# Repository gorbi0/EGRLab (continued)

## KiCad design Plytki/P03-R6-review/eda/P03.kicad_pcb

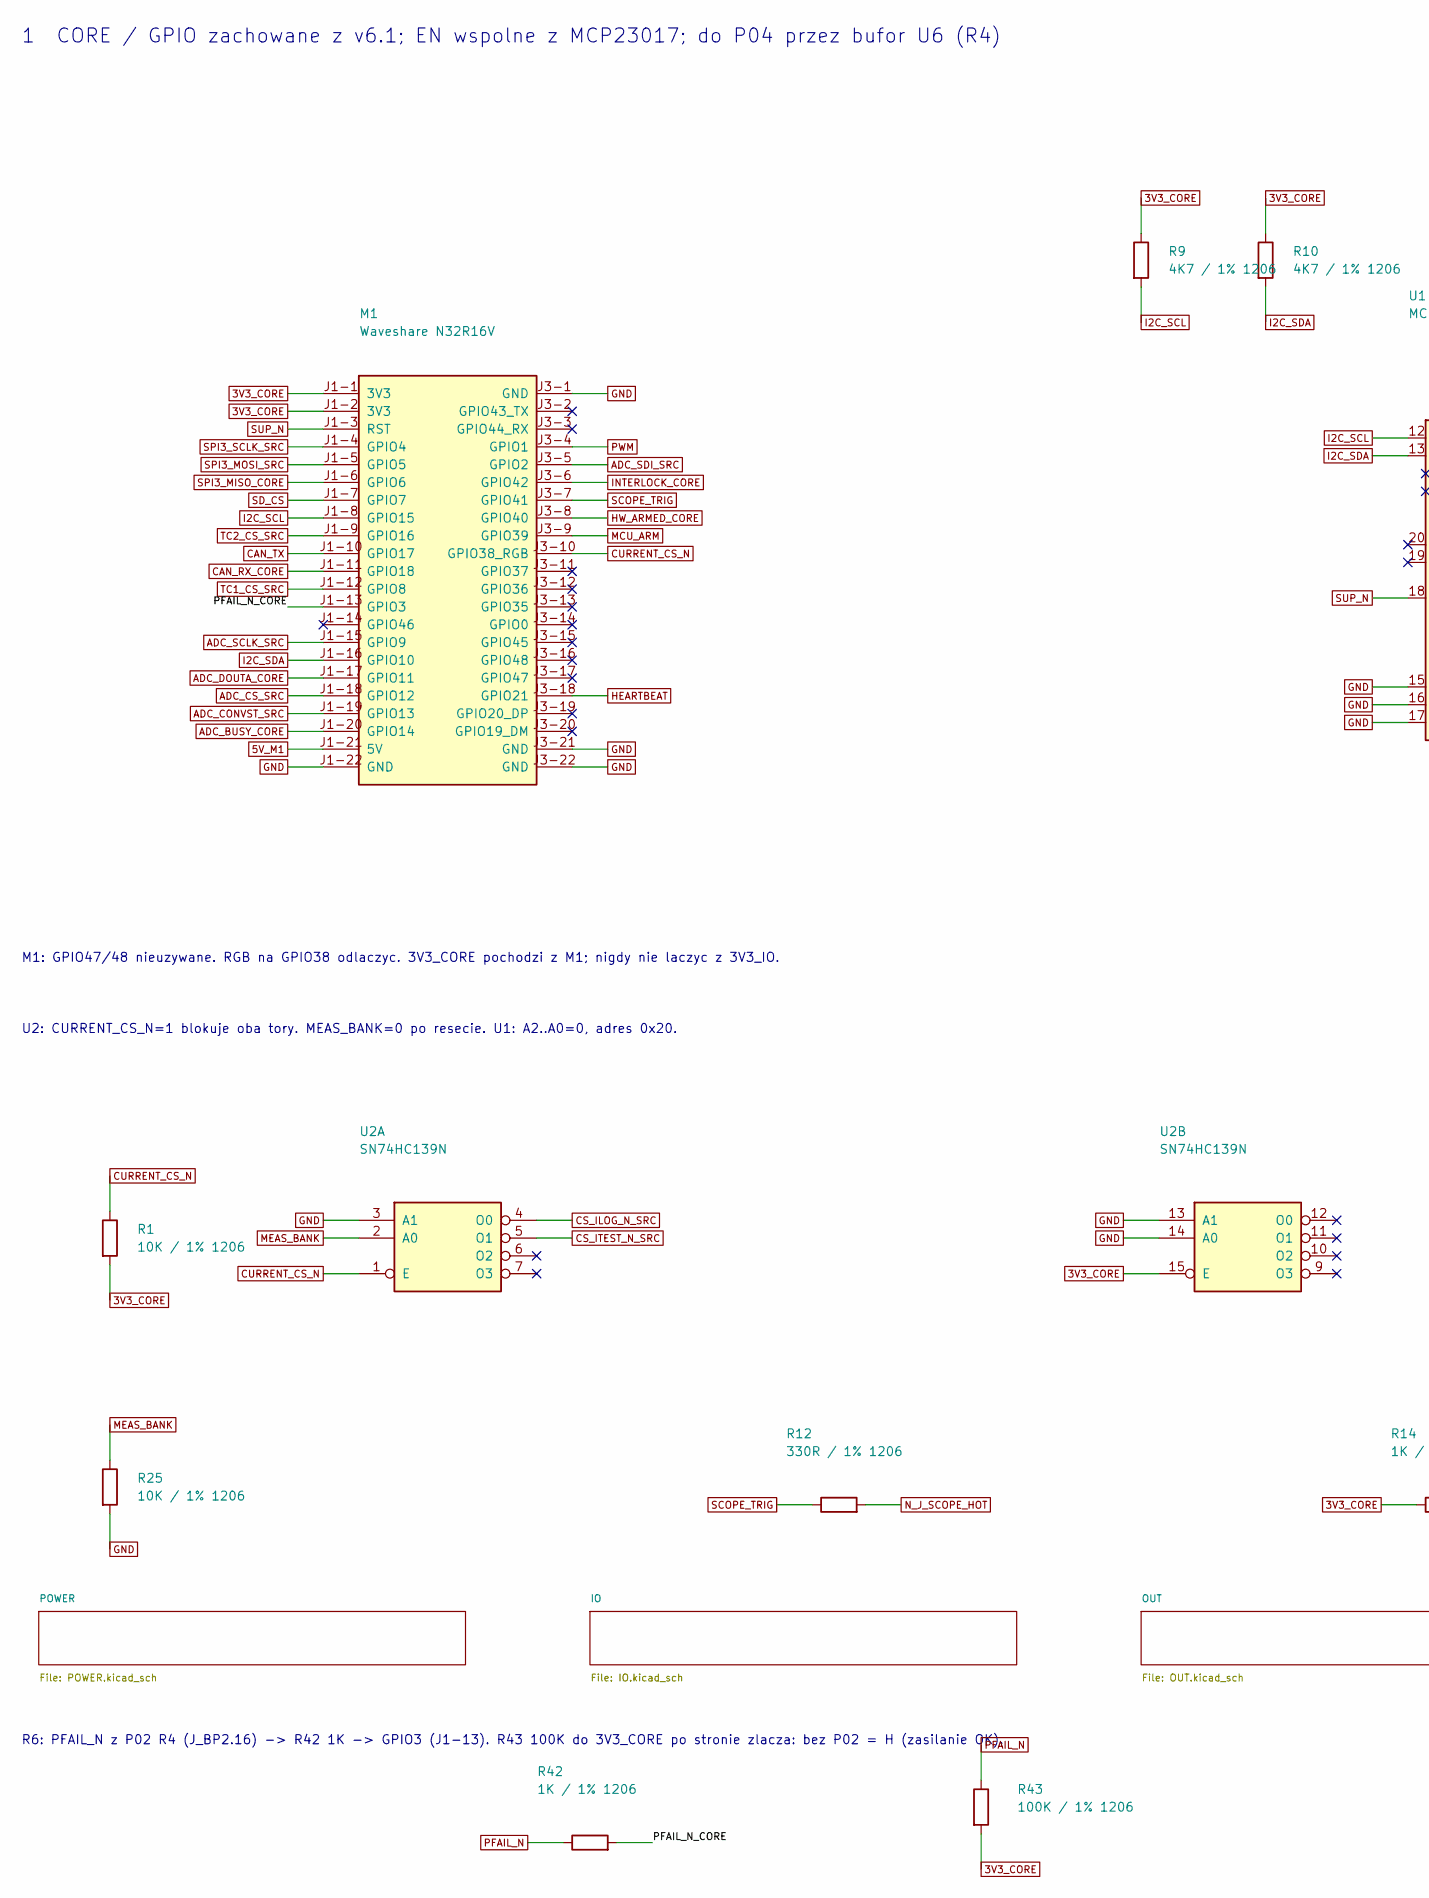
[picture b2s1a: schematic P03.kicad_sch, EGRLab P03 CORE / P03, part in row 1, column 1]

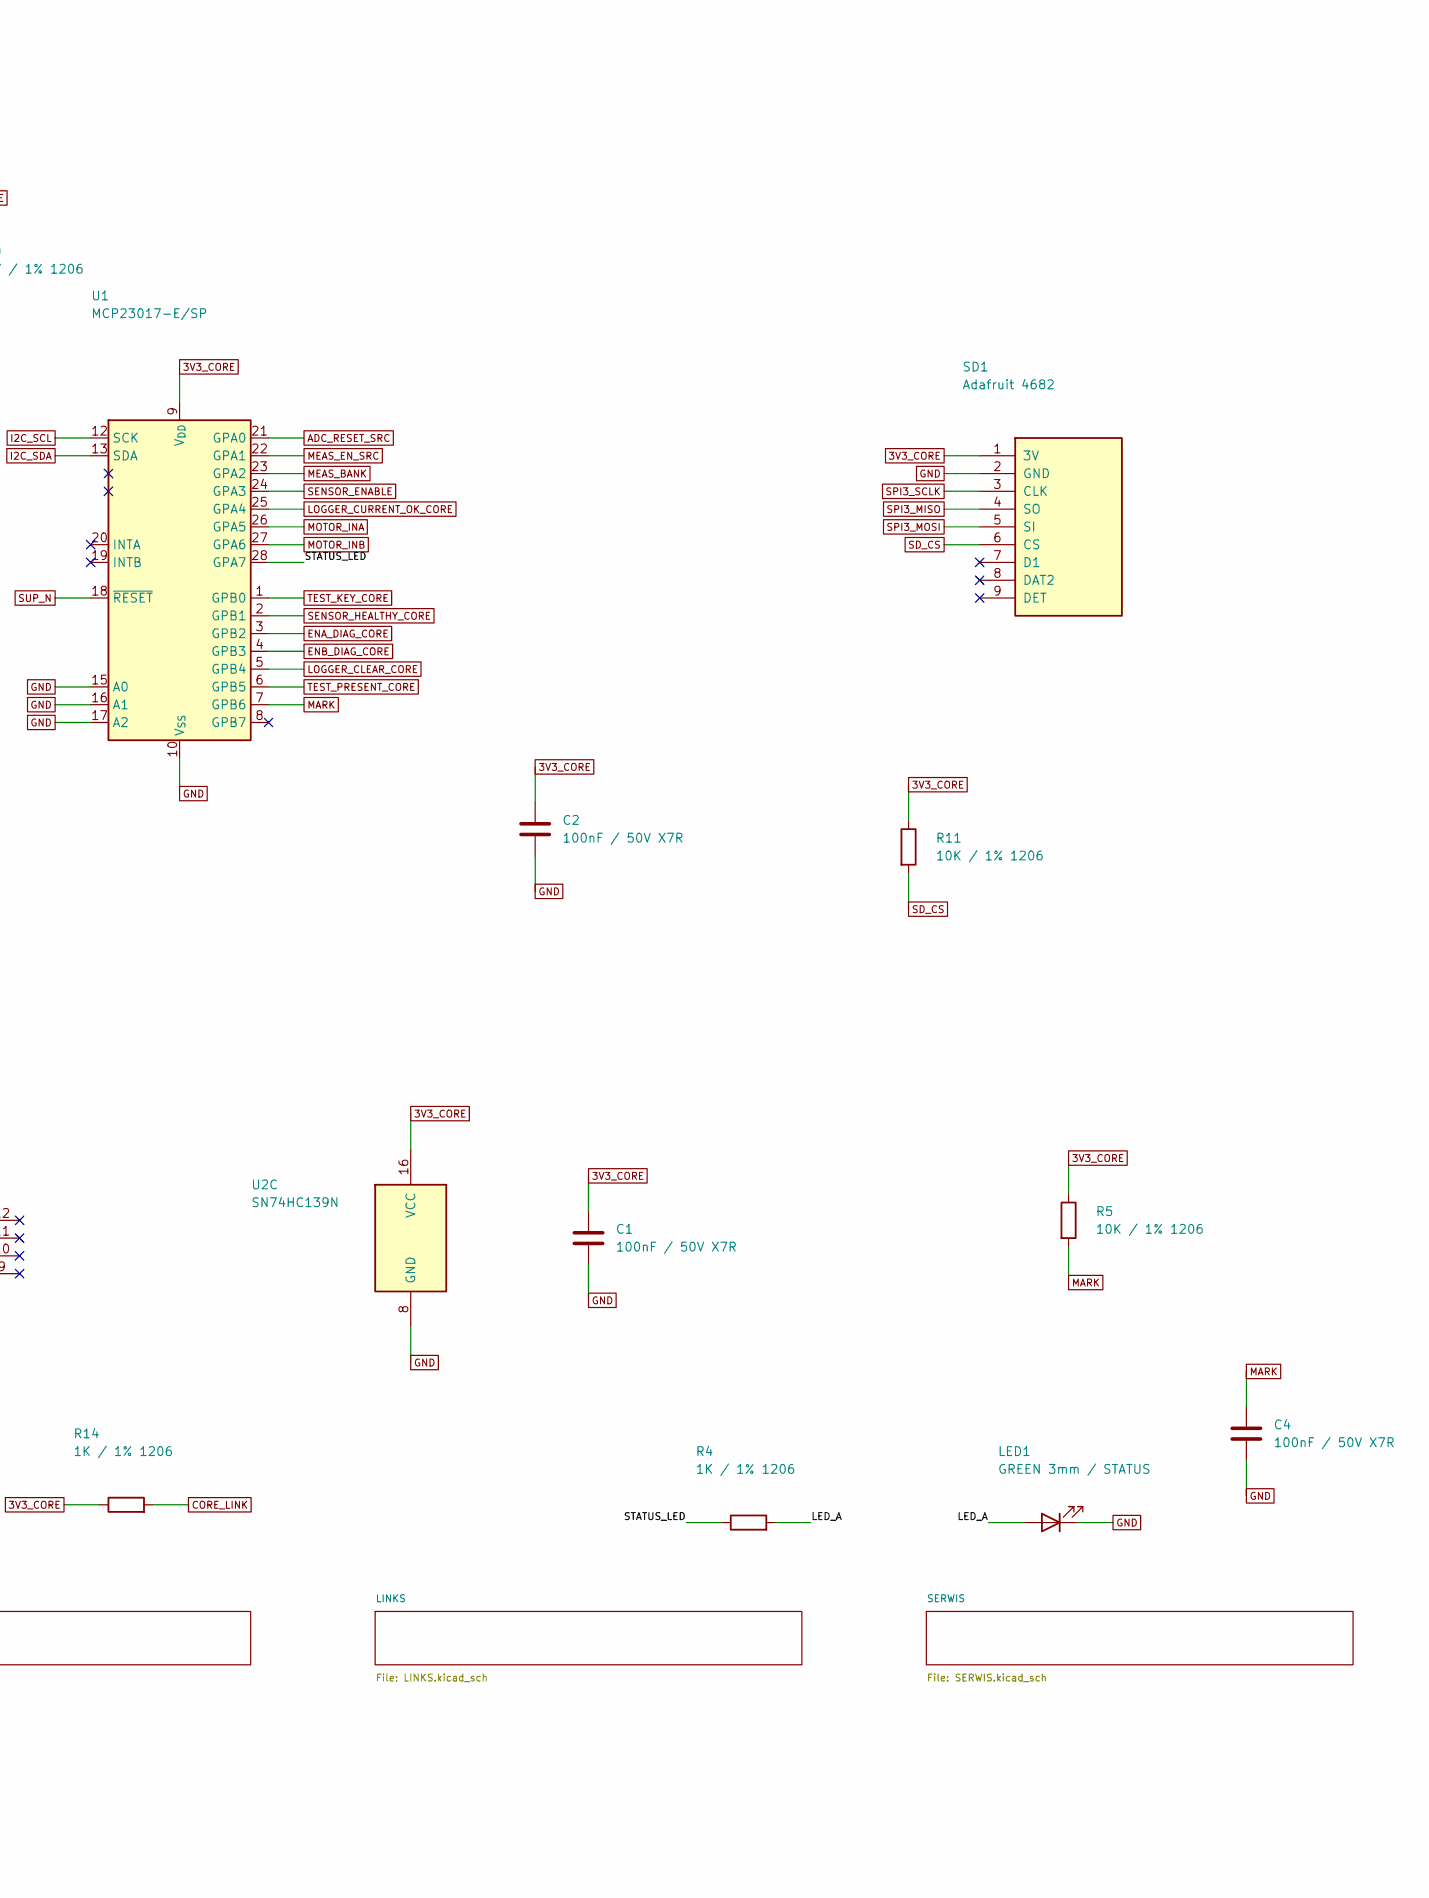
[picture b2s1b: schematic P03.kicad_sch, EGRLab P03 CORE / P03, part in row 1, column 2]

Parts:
C1, C2, C4: 100nF / 50V X7R; C_1206_3216Metric_Pad1.33x1.80mm_HandSolder; MPN GRM31CR71H104KA01L
LED1: GREEN 3mm / STATUS; LED_D3.0mm; MPN L-934GD
M1: Waveshare N32R16V; Waveshare_ESP32-S3-DEV-KIT_2x22_W22.86; MPN owned (Waveshare ESP32-S3-DEV-KIT-N32R1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
R1, R5, R11, R25: 10K / 1% 1206; R_1206_3216Metric_Pad1.30x1.75mm_HandSolder; MPN RC1206FR-0710KL
R4, R14, R42: 1K / 1% 1206; R_1206_3216Metric_Pad1.30x1.75mm_HandSolder; MPN RC1206FR-071KL
R9, R10: 4K7 / 1% 1206; R_1206_3216Metric_Pad1.30x1.75mm_HandSolder; MPN RC1206FR-074K7L
R12: 330R / 1% 1206; R_1206_3216Metric_Pad1.30x1.75mm_HandSolder; MPN RC1206FR-07330RL
R43: 100K / 1% 1206; R_1206_3216Metric_Pad1.30x1.75mm_HandSolder; MPN RC1206FR-07100KL
SD1: Adafruit 4682; Adafruit_4682_microSD_1x09; MPN Adafruit 4682 on a 1x9 female header + 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
U1: MCP23017-E/SP; DIP-28_W7.62mm; MPN MCP23017-E/SP
U2: SN74HC139N; DIP-16_W7.62mm; MPN SN74HC139N

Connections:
3V3_CORE: C1.1, C2.1, M1.J1-1 (3V3), M1.J1-2 (3V3), R1.2, R5.1, R9.1, R10.1, R11.1, R14.1, R43.2, SD1.1 (3V), U1.9 (V_{DD}), U2.15 (E), U2.16 (VCC); also elsewhere on the board
5V_M1: M1.J1-21 (5V); also elsewhere on the board
/LED_A: LED1.2 (A), R4.2
/PFAIL_N_CORE: M1.J1-13 (GPIO3), R42.2
/STATUS_LED: R4.1, U1.28 (GPA7)
ADC_BUSY_CORE: M1.J1-20 (GPIO14); also elsewhere on the board
ADC_CONVST_SRC: M1.J1-19 (GPIO13); also elsewhere on the board
ADC_CS_SRC: M1.J1-18 (GPIO12); also elsewhere on the board
ADC_DOUTA_CORE: M1.J1-17 (GPIO11); also elsewhere on the board
ADC_RESET_SRC: U1.21 (GPA0); also elsewhere on the board
ADC_SCLK_SRC: M1.J1-15 (GPIO9); also elsewhere on the board
ADC_SDI_SRC: M1.J3-5 (GPIO2); also elsewhere on the board
CAN_RX_CORE: M1.J1-11 (GPIO18); also elsewhere on the board
CAN_TX: M1.J1-10 (GPIO17); also elsewhere on the board
CORE_LINK: R14.2; also elsewhere on the board
CS_ILOG_N_SRC: U2.4 (O0); also elsewhere on the board
CS_ITEST_N_SRC: U2.5 (O1); also elsewhere on the board
CURRENT_CS_N: M1.J3-10 (GPIO38_RGB), R1.1, U2.1 (E); also elsewhere on the board
ENA_DIAG_CORE: U1.3 (GPB2); also elsewhere on the board
ENB_DIAG_CORE: U1.4 (GPB3); also elsewhere on the board
HEARTBEAT: M1.J3-18 (GPIO21); also elsewhere on the board
HW_ARMED_CORE: M1.J3-8 (GPIO40); also elsewhere on the board
I2C_SCL: M1.J1-8 (GPIO15), R9.2, U1.12 (SCK); also elsewhere on the board
I2C_SDA: M1.J1-16 (GPIO10), R10.2, U1.13 (SDA); also elsewhere on the board
INTERLOCK_CORE: M1.J3-6 (GPIO42); also elsewhere on the board
LOGGER_CLEAR_CORE: U1.5 (GPB4); also elsewhere on the board
LOGGER_CURRENT_OK_CORE: U1.25 (GPA4); also elsewhere on the board
MARK: C4.1, R5.2, U1.7 (GPB6); also elsewhere on the board
MCU_ARM: M1.J3-9 (GPIO39); also elsewhere on the board
MEAS_BANK: R25.1, U1.23 (GPA2), U2.2 (A0); also elsewhere on the board
MEAS_EN_SRC: U1.22 (GPA1); also elsewhere on the board
MOTOR_INA: U1.26 (GPA5); also elsewhere on the board
MOTOR_INB: U1.27 (GPA6); also elsewhere on the board
N_J_SCOPE_HOT: R12.2; also elsewhere on the board
PWM: M1.J3-4 (GPIO1); also elsewhere on the board
SCOPE_TRIG: M1.J3-7 (GPIO41), R12.1; also elsewhere on the board
SD_CS: M1.J1-7 (GPIO7), R11.2, SD1.6 (CS); also elsewhere on the board
SENSOR_ENABLE: U1.24 (GPA3); also elsewhere on the board
SENSOR_HEALTHY_CORE: U1.2 (GPB1); also elsewhere on the board
SPI3_MISO: SD1.4 (SO); also elsewhere on the board
SPI3_MISO_CORE: M1.J1-6 (GPIO6); also elsewhere on the board
SPI3_MOSI: SD1.5 (SI); also elsewhere on the board
SPI3_MOSI_SRC: M1.J1-5 (GPIO5); also elsewhere on the board
SPI3_SCLK: SD1.3 (CLK); also elsewhere on the board
SPI3_SCLK_SRC: M1.J1-4 (GPIO4); also elsewhere on the board
TC1_CS_SRC: M1.J1-12 (GPIO8); also elsewhere on the board
TC2_CS_SRC: M1.J1-9 (GPIO16); also elsewhere on the board
TEST_KEY_CORE: U1.1 (GPB0); also elsewhere on the board
TEST_PRESENT_CORE: U1.6 (GPB5); also elsewhere on the board

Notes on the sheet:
1 CORE / GPIO zachowane z v6.1; EN wspolne z MCP23017; do P04 przez bufor U6 (R4)
M1: GPIO47/48 nieuzywane. RGB na GPIO38 odlaczyc. 3V3_CORE pochodzi z M1; nigdy nie laczyc z 3V3_IO.
U2: CURRENT_CS_N=1 blokuje oba tory. MEAS_BANK=0 po resecie. U1: A2..A0=0, adres 0x20.
R6: PFAIL_N z P02 R4 (J_BP2.16) -> R42 1K -> GPIO3 (J1-13). R43 100K do 3V3_CORE po stronie zlacza: bez P02 = H (zasilanie OK).

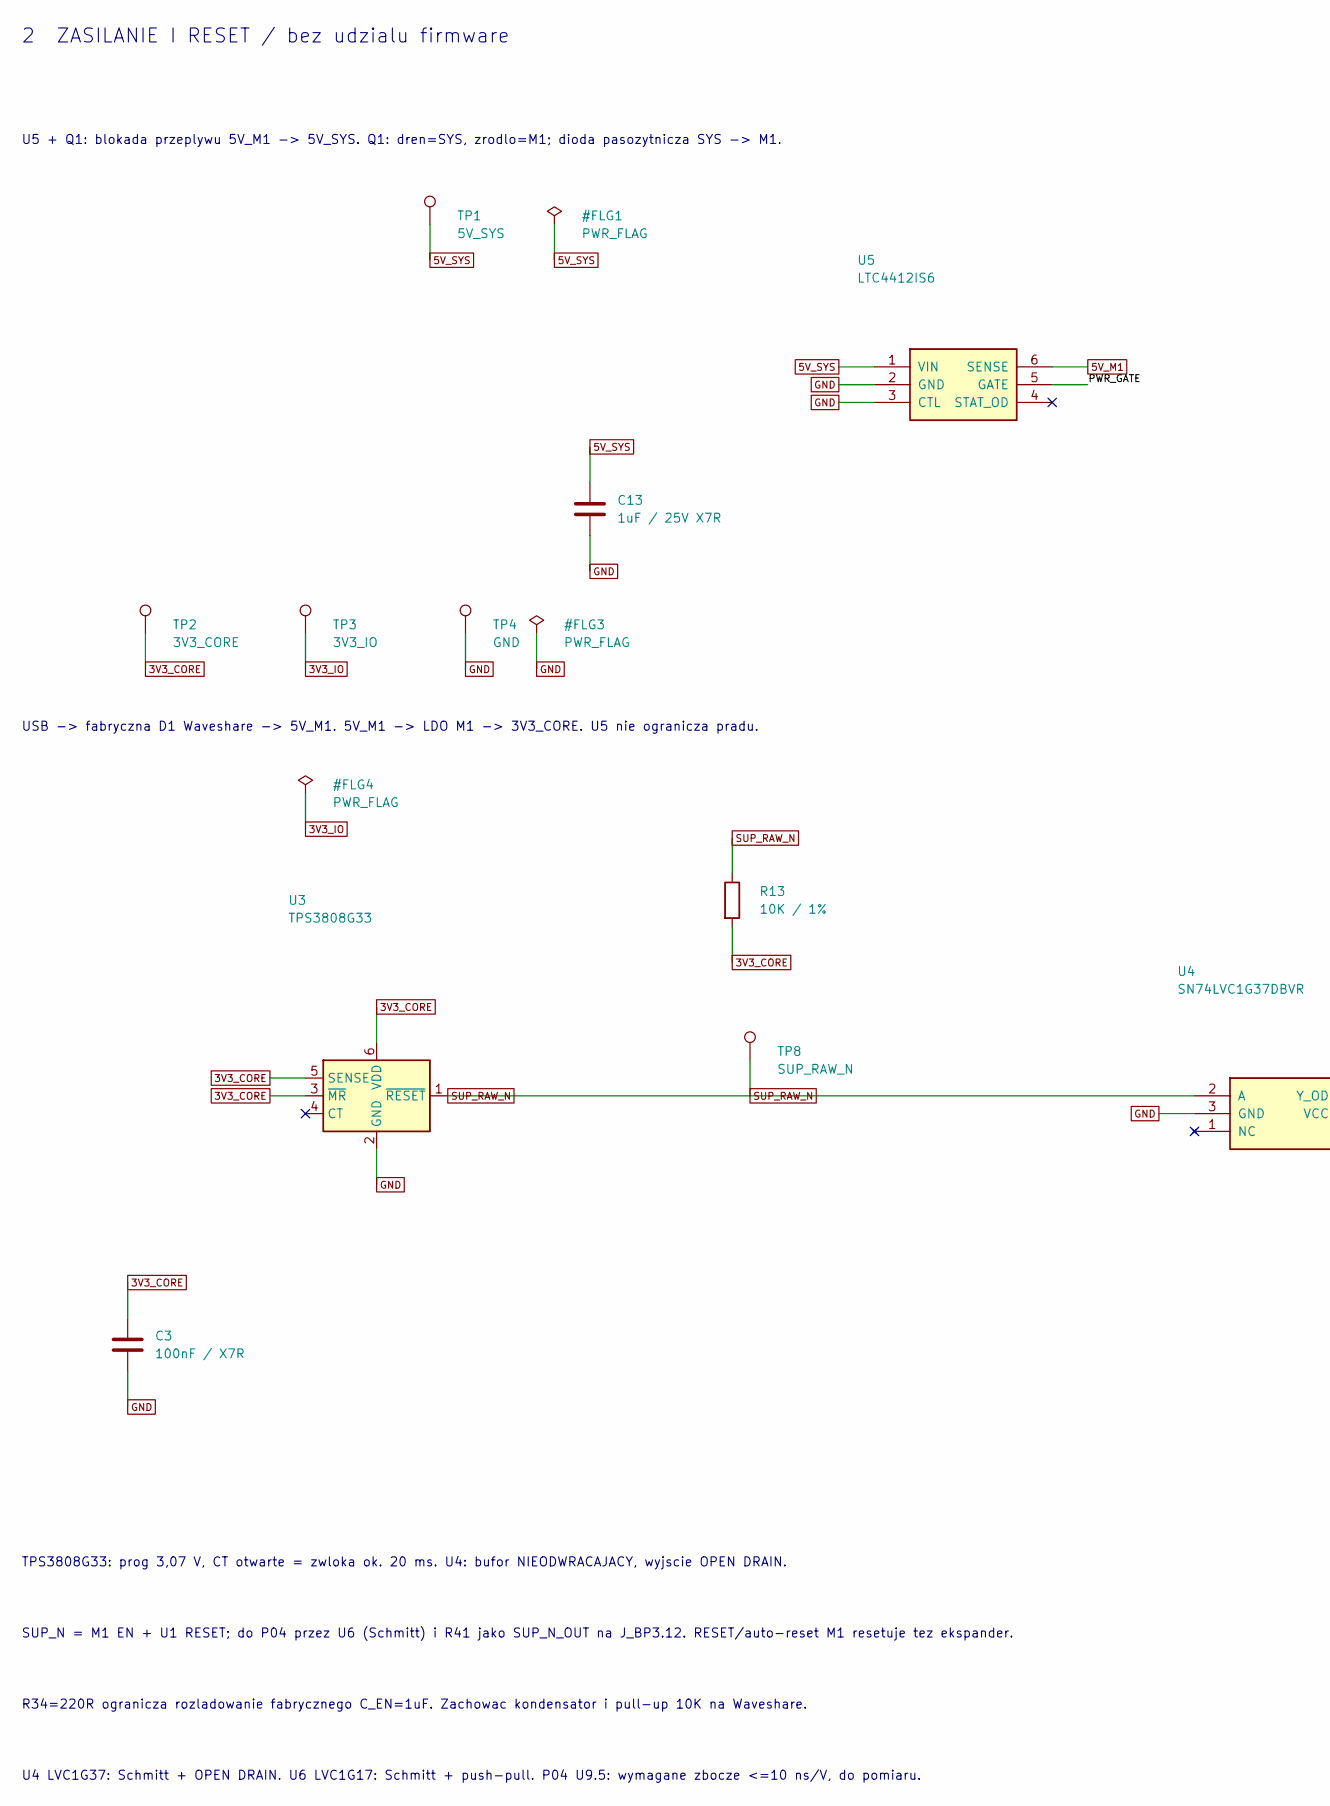
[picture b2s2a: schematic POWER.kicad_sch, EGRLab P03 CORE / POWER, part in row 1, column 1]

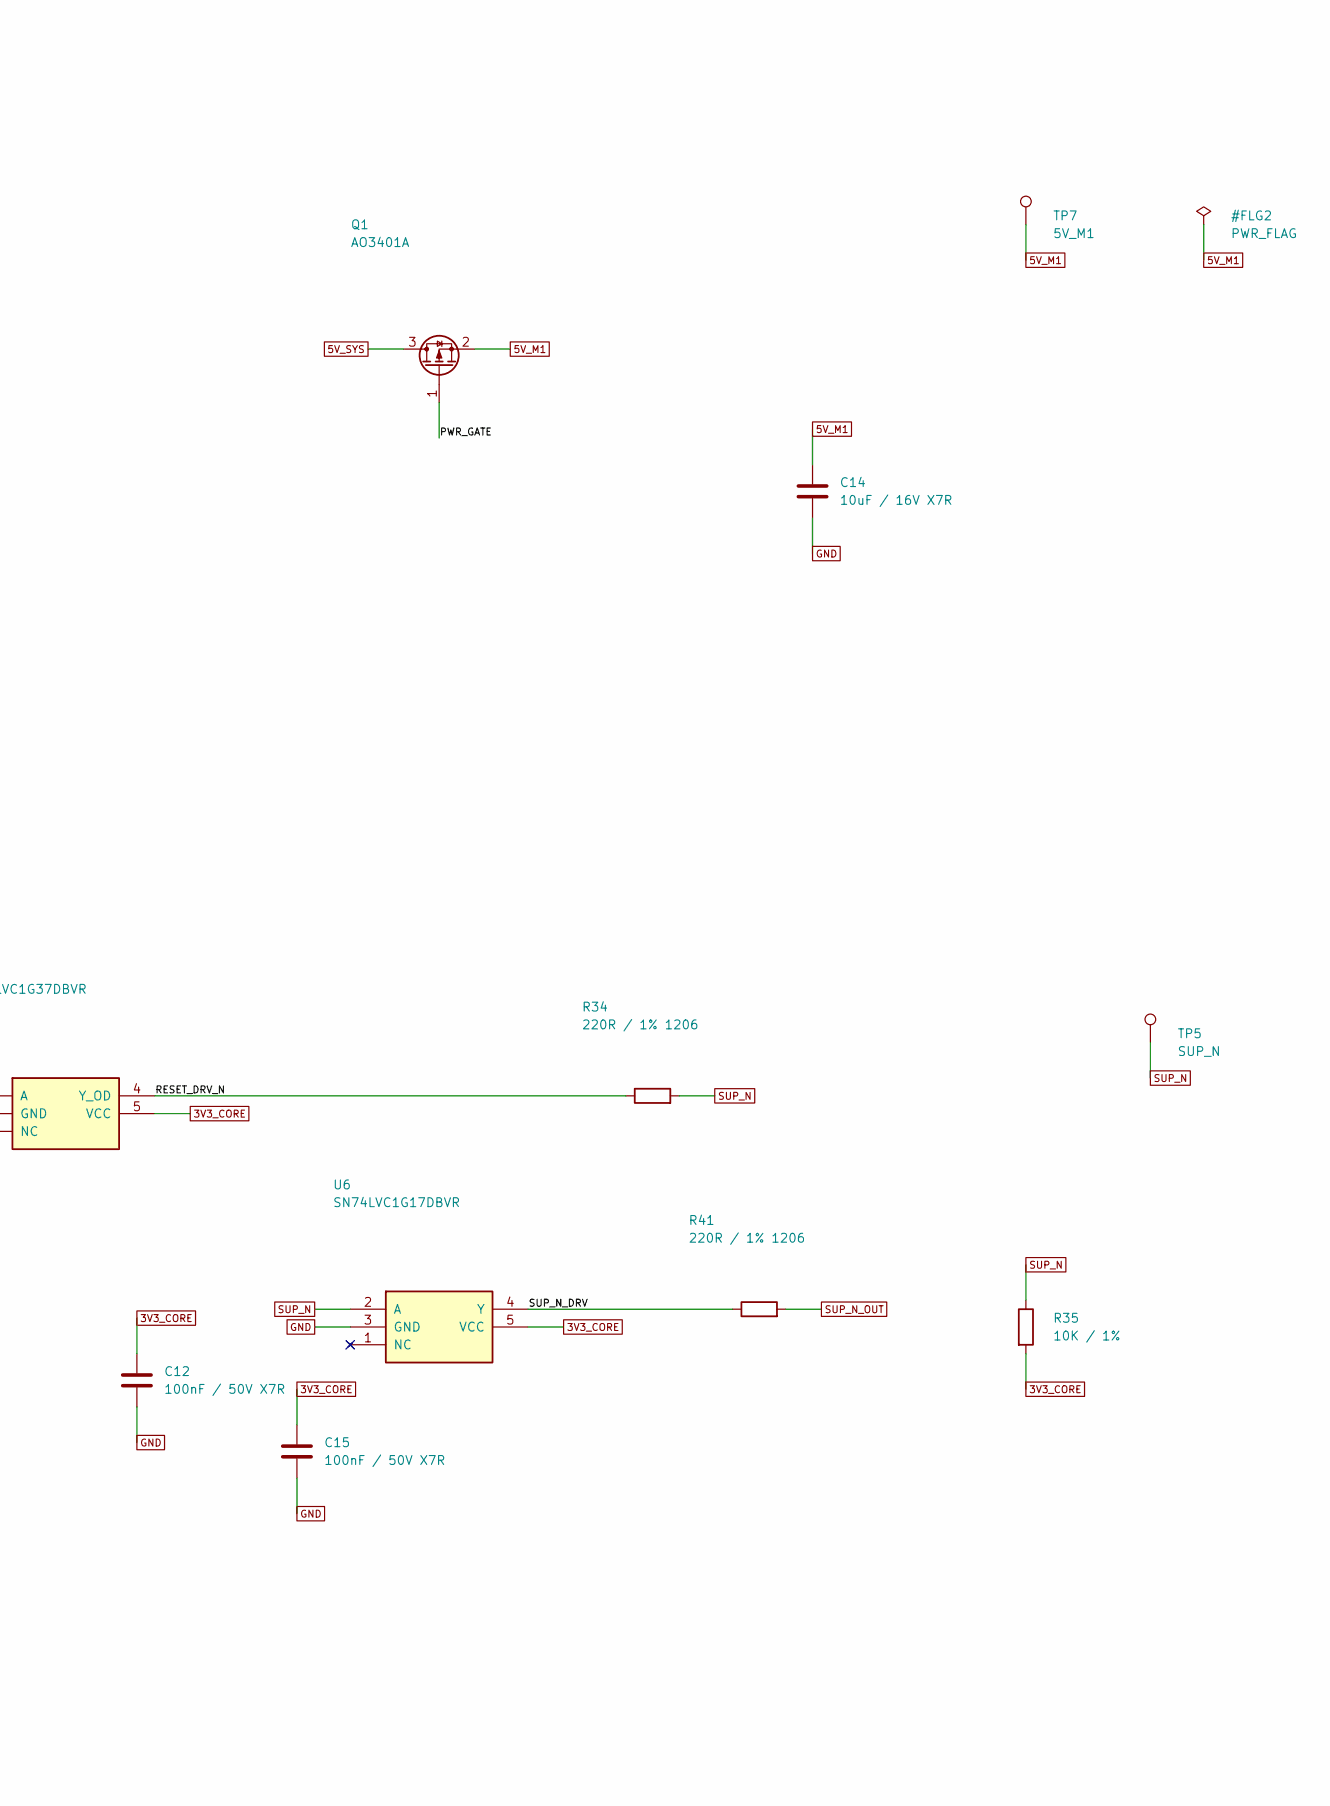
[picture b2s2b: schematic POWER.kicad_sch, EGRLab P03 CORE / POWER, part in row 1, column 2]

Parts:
C3: 100nF / X7R; C_Vishay_K15_H5_P5; MPN K104K15X7RF5TH5
C12, C15: 100nF / 50V X7R; C_1206_3216Metric_Pad1.33x1.80mm_HandSolder; MPN GRM31CR71H104KA01L
C13: 1uF / 25V X7R; C_1206_3216Metric_Pad1.33x1.80mm_HandSolder; MPN GRM31CR71E105KA12L
C14: 10uF / 16V X7R; C_1206_3216Metric_Pad1.33x1.80mm_HandSolder; MPN GRM31CR71C106KA12L
Q1: AO3401A; SOT-23; MPN AO3401A
R13, R35: 10K / 1%; R_Axial_DIN0207_L6.3mm_D2.5mm_P5.08mm_Vertical; MPN MF0207FTE-10K
R34, R41: 220R / 1% 1206; R_1206_3216Metric_Pad1.30x1.75mm_HandSolder; MPN RC1206FR-07220RL
TP1: 5V_SYS; TestPad_1; MPN PCB test pad
TP2: 3V3_CORE; TestPad_1; MPN PCB test pad
TP3: 3V3_IO; TestPad_1; MPN PCB test pad
TP4: GND; TestPad_1; MPN PCB test pad
TP5: SUP_N; TestPad_1; MPN PCB test pad
TP7: 5V_M1; TestPad_1; MPN PCB test pad
TP8: SUP_RAW_N; TestPad_1; MPN PCB test pad
U3: TPS3808G33; SOT-23-6; MPN TPS3808G33DBVR
U4: SN74LVC1G37DBVR; SOT-23-5; MPN SN74LVC1G37DBVR
U5: LTC4412IS6; SOT-23-6; MPN LTC4412IS6#TRPBF
U6: SN74LVC1G17DBVR; SOT-23-5; MPN SN74LVC1G17DBVR

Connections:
3V3_CORE: C3.1, C12.1, C15.1, R13.2, R35.2, TP2.1, U3.3 (~MR), U3.5 (SENSE), U3.6 (VDD), U4.5 (VCC), U6.5 (VCC); also elsewhere on the board
3V3_IO: TP3.1; also elsewhere on the board
5V_M1: C14.1, Q1.2 (S), TP7.1, U5.6 (SENSE); also elsewhere on the board
/POWER/PWR_GATE: Q1.1 (G), U5.5 (GATE)
/POWER/RESET_DRV_N: R34.1, U4.4 (Y_OD)
/POWER/SUP_N_DRV: R41.1, U6.4 (Y)
SUP_N_OUT: R41.2; also elsewhere on the board
SUP_RAW_N: R13.1, TP8.1, U3.1 (~RESET), U4.2 (A); also elsewhere on the board

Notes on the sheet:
2 ZASILANIE I RESET / bez udzialu firmware
U5 + Q1: blokada przeplywu 5V_M1 -> 5V_SYS. Q1: dren=SYS, zrodlo=M1; dioda pasozytnicza SYS -> M1.
USB -> fabryczna D1 Waveshare -> 5V_M1. 5V_M1 -> LDO M1 -> 3V3_CORE. U5 nie ogranicza pradu.
TPS3808G33: prog 3,07 V, CT otwarte = zwloka ok. 20 ms. U4: bufor NIEODWRACAJACY, wyjscie OPEN DRAIN.
SUP_N = M1 EN + U1 RESET; do P04 przez U6 (Schmitt) i R41 jako SUP_N_OUT na J_BP3.12. RESET/auto-reset M1 resetuje tez ekspander.
R34=220R ogranicza rozladowanie fabrycznego C_EN=1uF. Zachowac kondensator i pull-up 10K na Waveshare.
U4 LVC1G37: Schmitt + OPEN DRAIN. U6 LVC1G17: Schmitt + push-pull. P04 U9.5: wymagane zbocze <=10 ns/V, do pomiaru.

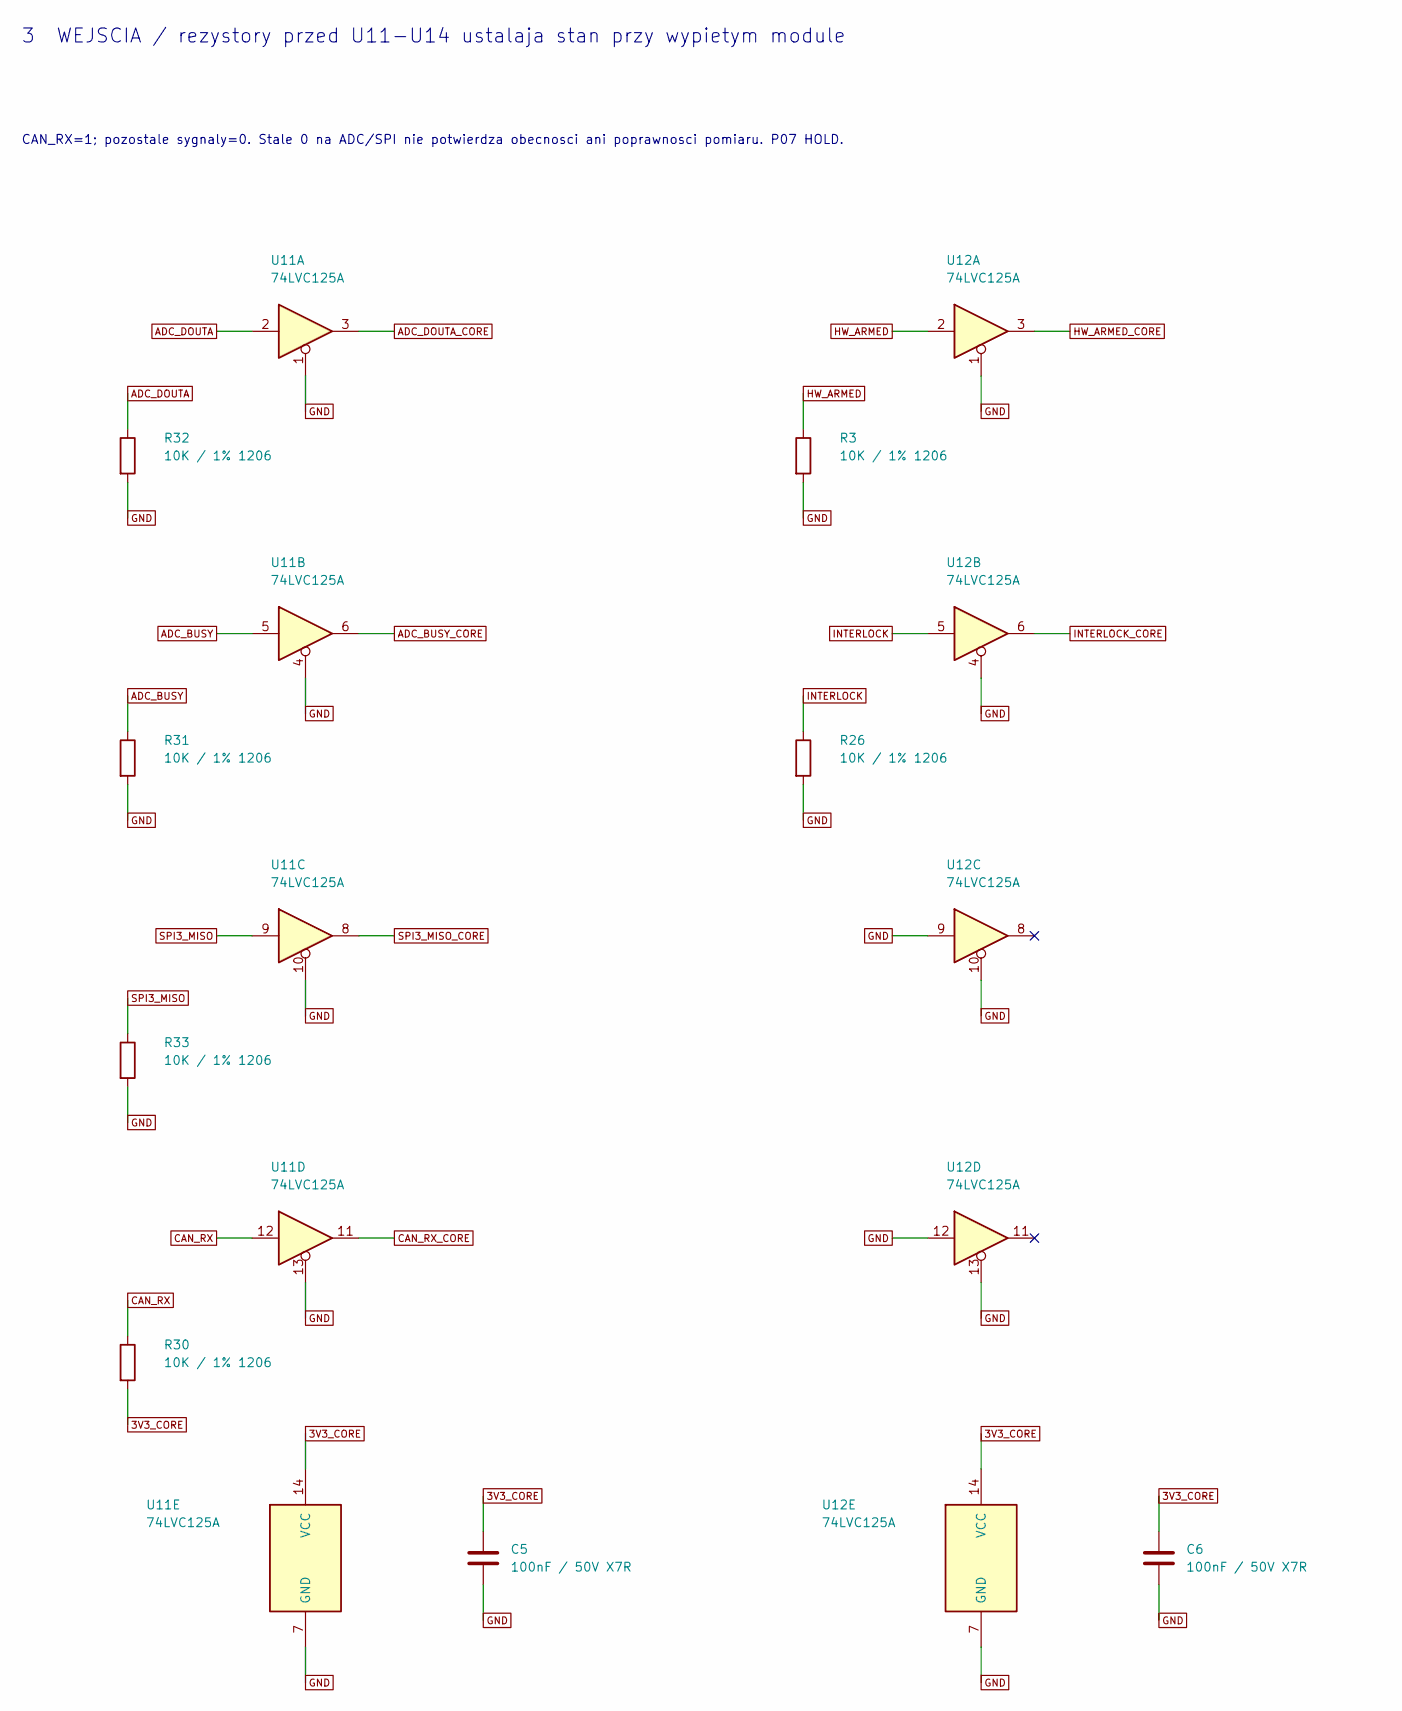
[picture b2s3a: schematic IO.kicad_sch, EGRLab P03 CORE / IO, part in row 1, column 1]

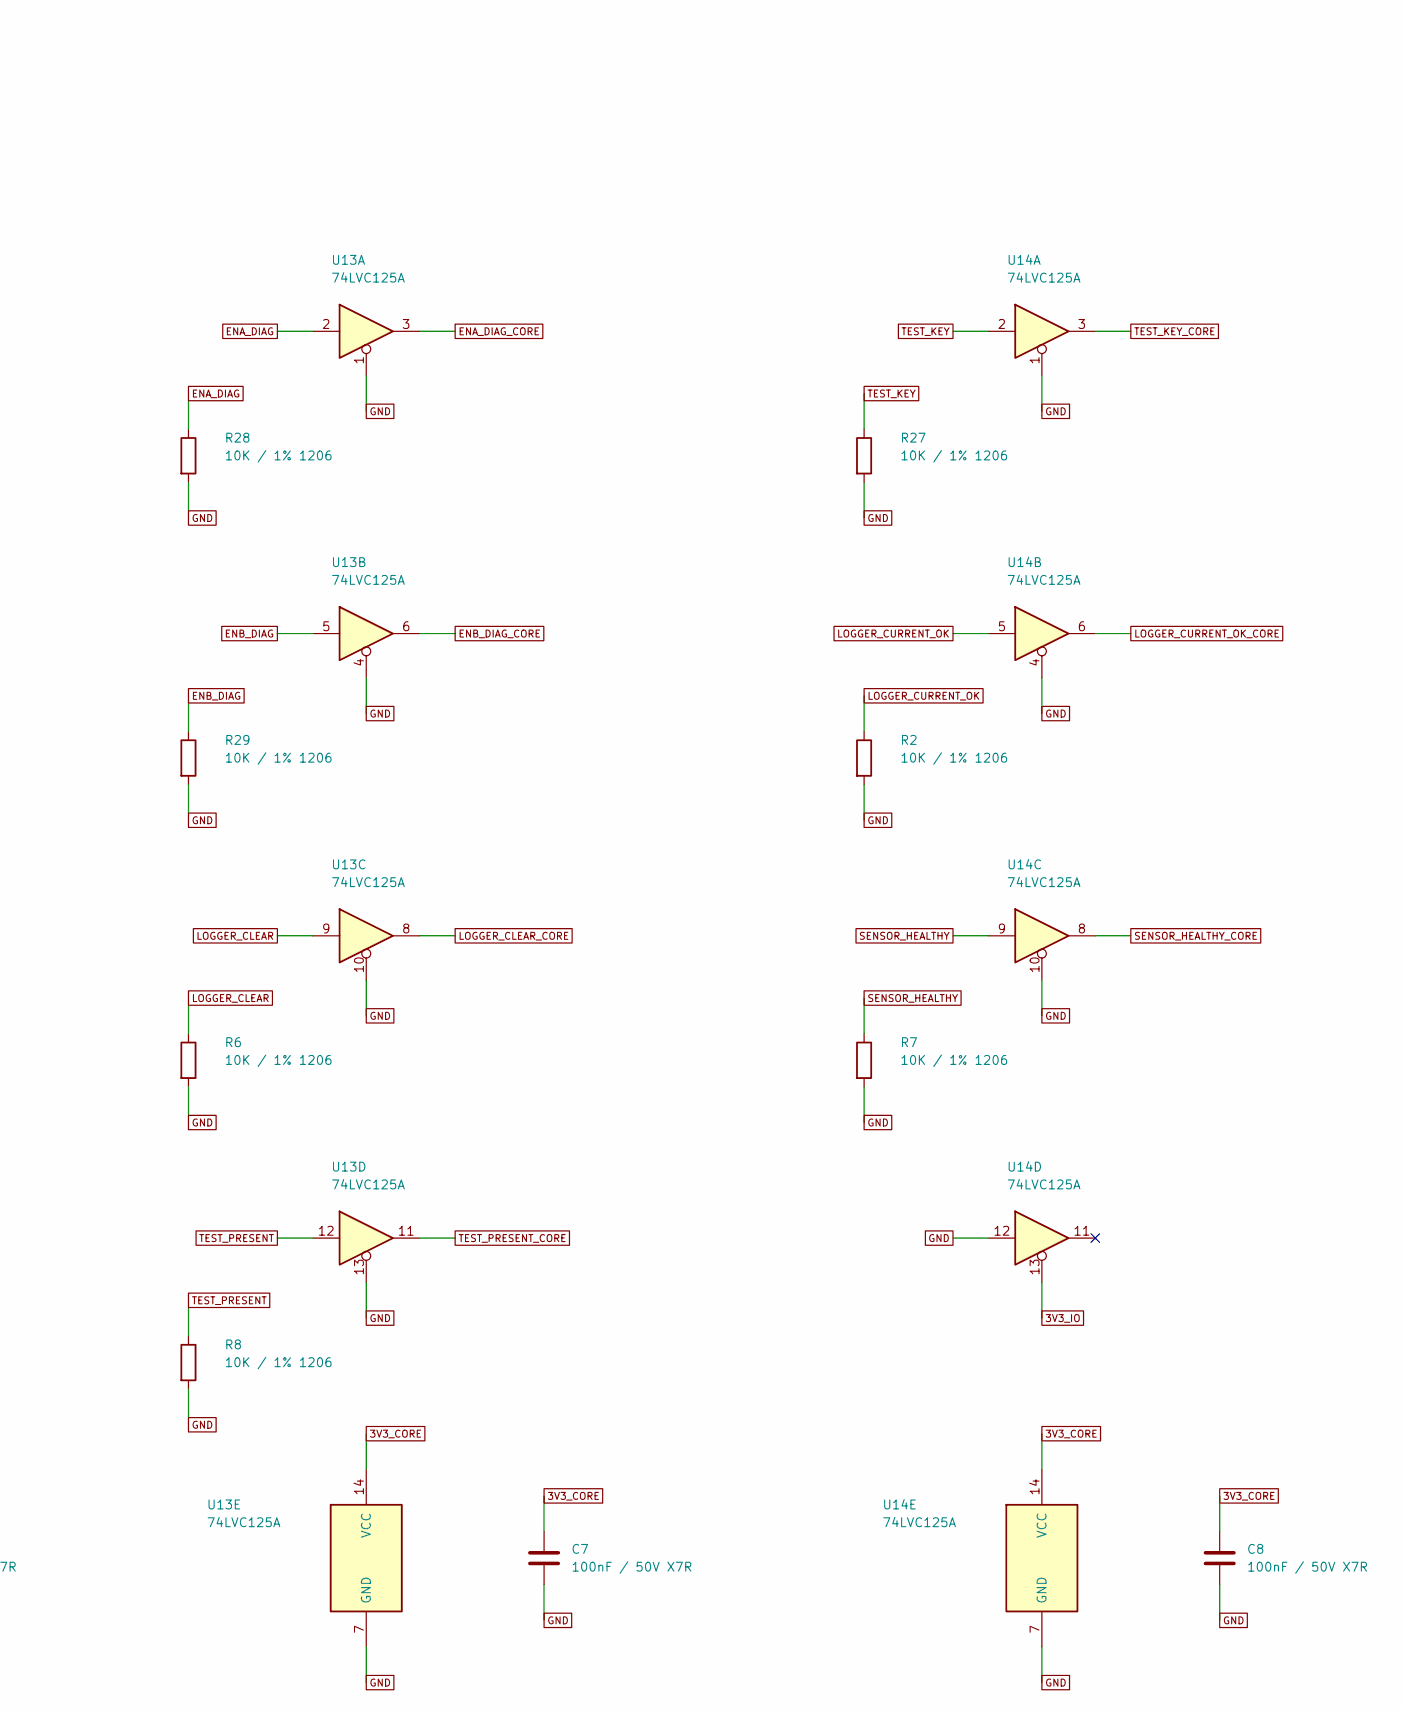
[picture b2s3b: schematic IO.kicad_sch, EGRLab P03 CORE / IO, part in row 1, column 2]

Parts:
C5, C6, C7, C8: 100nF / 50V X7R; C_1206_3216Metric_Pad1.33x1.80mm_HandSolder; MPN GRM31CR71H104KA01L
R2, R3, R6, R7, R8, R26, R27, R28, R29, R30, R31, R32, R33: 10K / 1% 1206; R_1206_3216Metric_Pad1.30x1.75mm_HandSolder; MPN RC1206FR-0710KL
U11, U12, U13, U14: 74LVC125A; SOIC-14_3.9x8.7mm_P1.27mm; MPN 74LVC125AD,118 (Nexperia)

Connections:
3V3_CORE: C5.1, C6.1, C7.1, C8.1, R30.2, U11.14 (VCC), U12.14 (VCC), U13.14 (VCC), U14.14 (VCC); also elsewhere on the board
3V3_IO: U14.13; also elsewhere on the board
ADC_BUSY: R31.1, U11.5; also elsewhere on the board
ADC_BUSY_CORE: U11.6; also elsewhere on the board
ADC_DOUTA: R32.1, U11.2; also elsewhere on the board
ADC_DOUTA_CORE: U11.3; also elsewhere on the board
CAN_RX: R30.1, U11.12; also elsewhere on the board
CAN_RX_CORE: U11.11; also elsewhere on the board
ENA_DIAG: R28.1, U13.2; also elsewhere on the board
ENA_DIAG_CORE: U13.3; also elsewhere on the board
ENB_DIAG: R29.1, U13.5; also elsewhere on the board
ENB_DIAG_CORE: U13.6; also elsewhere on the board
HW_ARMED: R3.1, U12.2; also elsewhere on the board
HW_ARMED_CORE: U12.3; also elsewhere on the board
INTERLOCK: R26.1, U12.5; also elsewhere on the board
INTERLOCK_CORE: U12.6; also elsewhere on the board
LOGGER_CLEAR: R6.1, U13.9; also elsewhere on the board
LOGGER_CLEAR_CORE: U13.8; also elsewhere on the board
LOGGER_CURRENT_OK_CORE: U14.6; also elsewhere on the board
SENSOR_HEALTHY: R7.1, U14.9; also elsewhere on the board
SENSOR_HEALTHY_CORE: U14.8; also elsewhere on the board
SPI3_MISO: R33.1, U11.9; also elsewhere on the board
SPI3_MISO_CORE: U11.8; also elsewhere on the board
TEST_KEY: R27.1, U14.2; also elsewhere on the board
TEST_KEY_CORE: U14.3; also elsewhere on the board
TEST_PRESENT: R8.1, U13.12; also elsewhere on the board
TEST_PRESENT_CORE: U13.11; also elsewhere on the board

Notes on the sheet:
3 WEJSCIA / rezystory przed U11-U14 ustalaja stan przy wypietym module
CAN_RX=1; pozostale sygnaly=0. Stale 0 na ADC/SPI nie potwierdza obecnosci ani poprawnosci pomiaru. P07 HOLD.
